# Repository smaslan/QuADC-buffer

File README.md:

# Precision Buffer with Low Input Capacitance

Following project is a precision buffer developed in scope of project EMPIR project QuADC (see documentation.pdf for details).

The main goal was flatness below 0.1 µV/V up to 10 kHz. Calibration uncertainty at 1 MHz requirement was 5 µV/V. Input capacitance as low as possible. Output impedance as low as possible. The circuit uses bootstrapping of the supply voltages which reduces errors significantly and also ensure very low apparent input shunting capacitance. Cost for the solution is limited stability. The buffer cannot be supplied from low impedance source otherwise it tends to oscillate. It designed as output bufffer for the resistive voltage dividers.

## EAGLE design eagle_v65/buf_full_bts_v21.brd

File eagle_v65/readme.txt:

Eagle files, version V6.5

Layers from top to bottom: top, route2, route15, bottom
Top silk: tPlace + tDoc + tNames
Bottom silk (not tested): bPlace + bNames

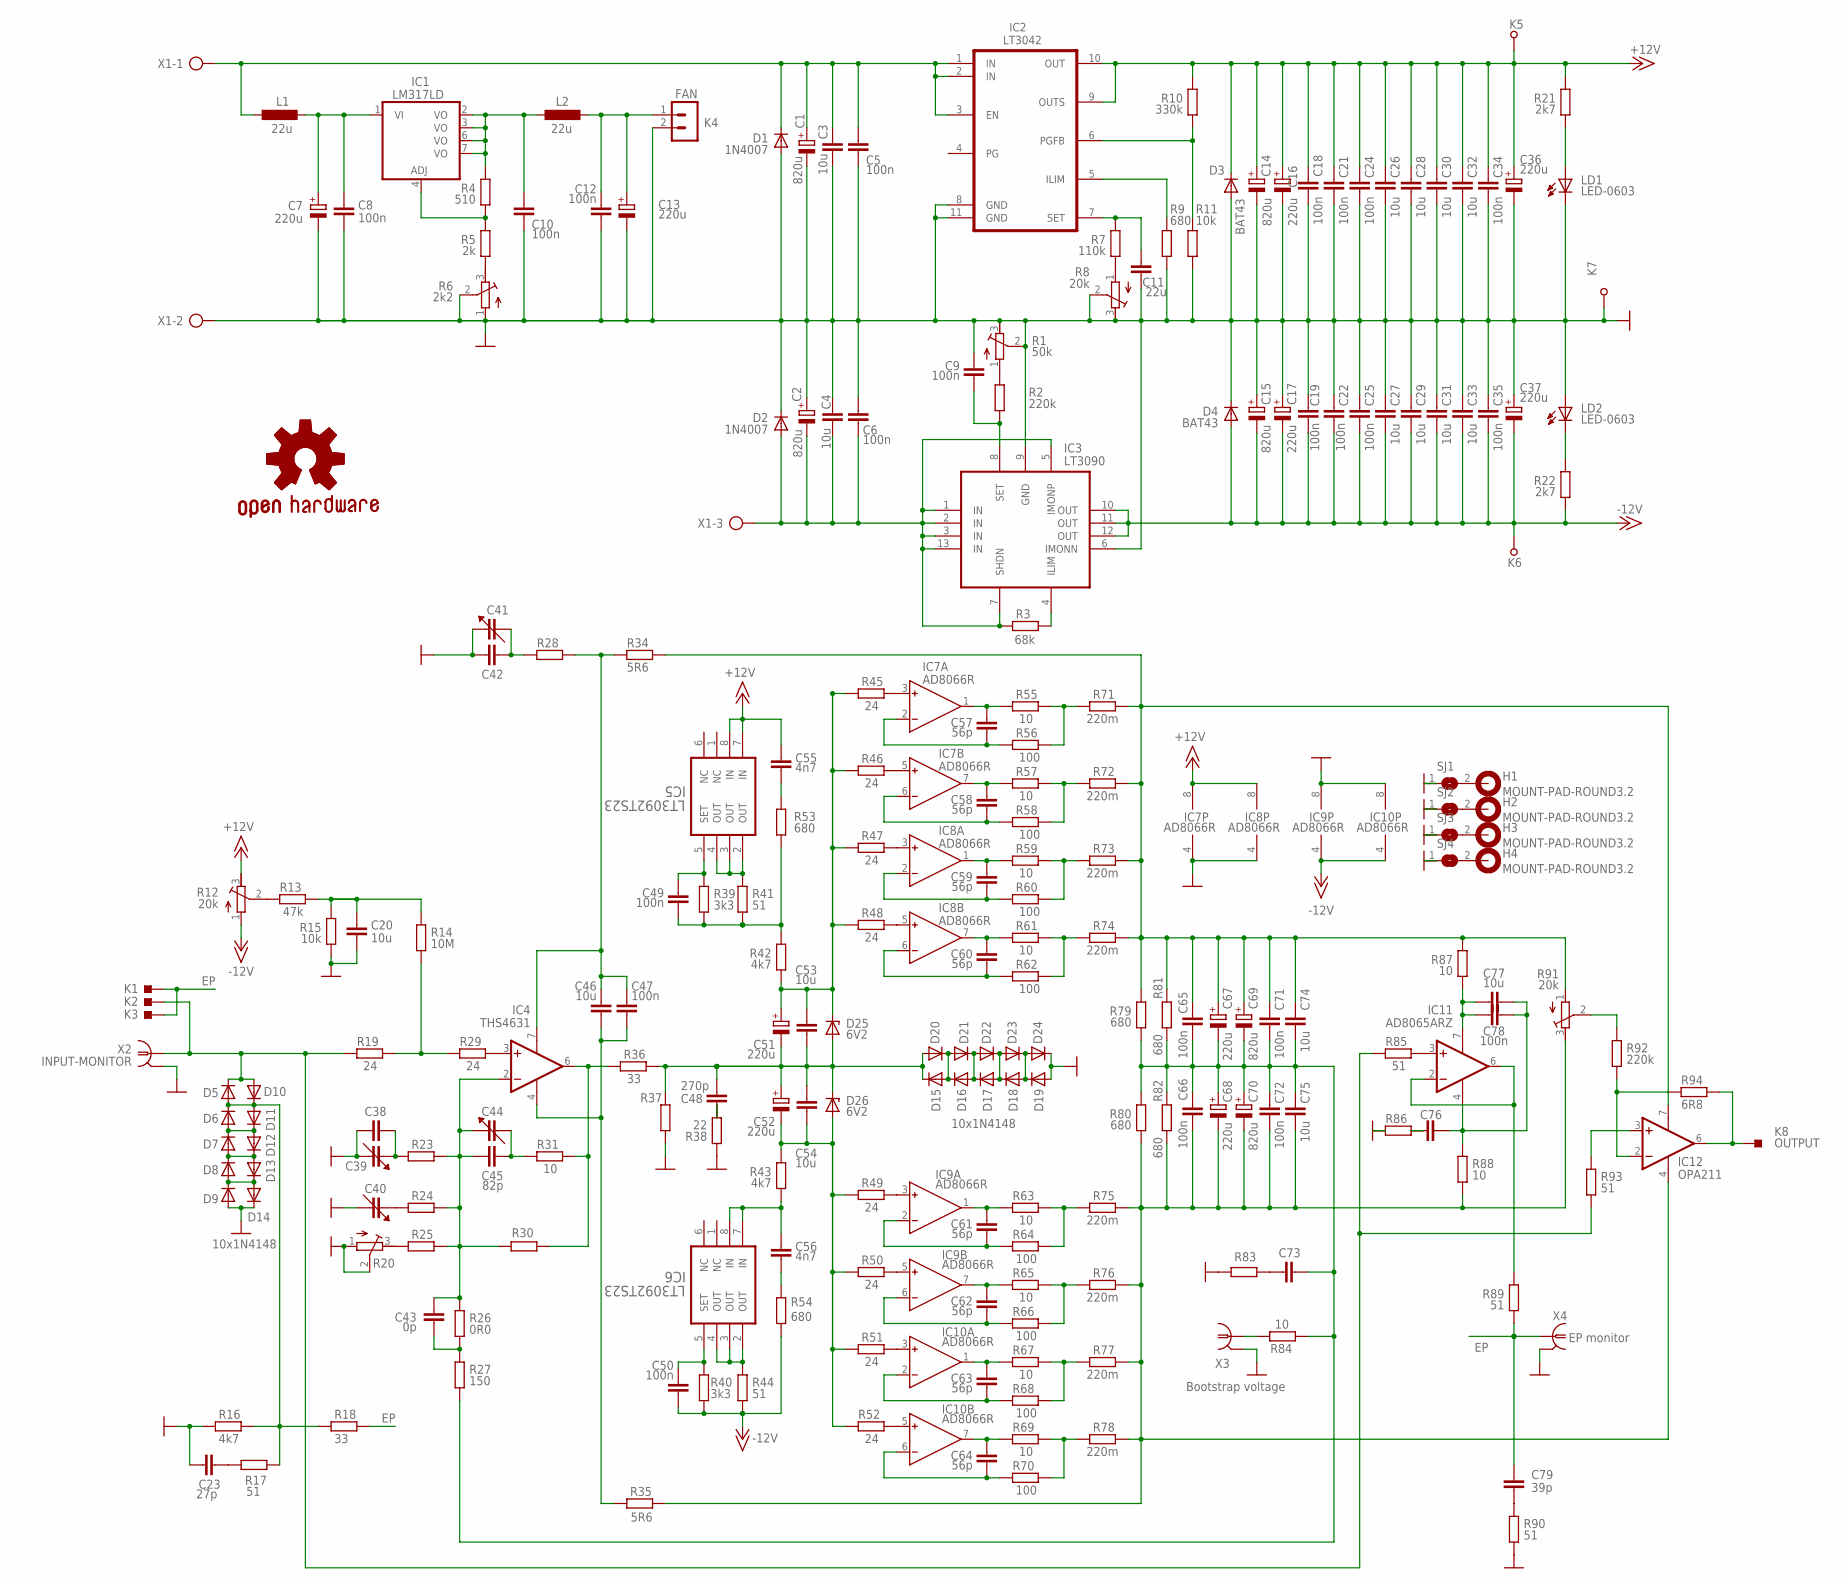
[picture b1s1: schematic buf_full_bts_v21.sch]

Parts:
C1, C2, C14, C15, C69, C70: 820u; E5-10,5
C3, C4, C20, C26, C27, C28, C29, C30, C31, C32, C33, C46, C53, C54, C74, C75, C77: 10u; C1210K
C5, C6, C8, C9, C10, C12, C18, C19, C21, C22, C24, C25, C34, C35, C47, C49, C50, C65, C66, C71, C72, C78: 100n; X0805
C7, C13, C16, C17, C36, C37, C51, C52, C67, C68: 220u; E2,5-7
C11: 22u; C1210K
C23: 27p; C025-024X044
C38, C42, C73, C76: C-EU025-024X044; C025-024X044
C39, C40, C41, C44: C_TRIMMER-9344; CTRIMMER9344
C43: 0p; C025-024X044
C45: 82p; C025-024X044
C48: 270p; X0805
C55, C56: 4n7; C025-024X044
C57, C58, C59, C60, C61, C62, C63, C64: 56p; C025-024X044
C79: 39p; C025-024X044
D1, D2: 1N4007; DO-214AC
D3, D4: BAT43; SOD80C
D5, D6, D7, D8, D9, D10, D11, D12, D13, D16, D17, D18, D19, D20, D21, D22, D23, D24: DIODE-MICROMELF-W; MICROMELF-W
D14, D15: 10x1N4148; MICROMELF-W
D25, D26: 6V2; SOD80C
GOLD_ORB_SM1: OSHWLOGO_GOLD_ORB_MED; OSHW1
H1, H2, H3, H4: MOUNT-PAD-ROUND3.2; 3,2-PAD
IC1: LM317LD; SO08
IC2: LT3042; SOP50P490X110-11N
IC3: LT3090; SOP65P490X110-13N
IC4: THS4631; SO8
IC5, IC6: LT3092TS23; SOT65P280X100-8N
IC7, IC8, IC9, IC10: AD8066R; SO8
IC11: AD8065ARZ; SO8
IC12: OPA211; SO8
K1, K3: SP_RI; SMD_1X1_S9
K2: SP_RH; SMD_1X1_S8
K4: FAN; MA02-1W
K5, K6, K7: SPP; SP_PRO
K8: OUTPUT; SMD_1X1_S8
L1, L2: 22u; L3225M
LD1, LD2: LED-0603; D0603
R1: 50k; RTRIM3214W
R2, R92: 220k; X0805
R3: 68k; X0805
R4: 510; X0805
R5: 2k; X0805
R6: 2k2; RT3364W
R7: 110k; X0805
R8, R12, R91: 20k; RTRIM3214W
R9, R79, R80, R81, R82: 680; X0805
R10: 330k; X0805
R11, R15: 10k; X0805
R13: 47k; X0805
R14: 10M; X0805
R16, R42, R43: 4k7; X0805
R17, R90: 51; 0207/2V
R18: 33; X0805
R19, R29, R45, R46, R47, R48, R49, R50, R51, R52: 24; X0805
R20: R-TRIMM3214W; RTRIM3214W
R21, R22: 2k7; X0805
R23, R24, R25, R28, R30, R37, R83, R86: R-EU_0207/2V; 0207/2V
R26: 0R0; 0207/2V
R27: 150; 0207/2V
R31, R55, R57, R59, R61, R63, R65, R67, R69, R84: 10; 0207/2V
R34, R35: 5R6; X0805
R36: 33; 0207/2V
R38: 22; X0805
R39, R40: 3k3; X0805
R41, R44, R85, R89, R93: 51; X0805
R53, R54: 680; 0207/2V
R56, R58, R60, R62, R64, R66, R68, R70: 100; 0207/2V
R71, R72, R73, R74, R75, R76, R77, R78: 220m; R1210
R87, R88: 10; X0805
R94: 6R8; X0805
SJ1, SJ2, SJ3, SJ4: SJ
X1: AK500/3
X2: INPUT-MONITOR; A1944
X3: Bootstrap voltage; A1944
X4: EP monitor; A1944

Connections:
+15V: C14.+, C16.+, C18.P$1 (1), C21.P$1 (1), C24.P$1 (1), C26.1, C28.1, C30.1, C32.1, C34.P$1 (1), C36.+, C55.1, D3.C, IC2.9 (OUTS), IC2.10 (OUT), IC5.7 (IN), IC5.8 (IN), IC7.8 (V+), IC8.8 (V+), K5.P$1, R10.P$2 (2), R12.3 (E), R21.P$2 (2)
+15V1: C56.1, IC6.7 (IN), IC6.8 (IN), R43.P$1 (1)
+15V2: C1.+, C3.1, C5.P$1 (1), D1.C, IC2.1 (IN), IC2.2 (IN), IC2.3 (EN), L1.1, X1.1
-15V: C15.-, C17.-, C19.P$2 (2), C22.P$2 (2), C25.P$2 (2), C27.2, C29.2, C31.2, C33.2, C35.P$2 (2), C37.-, C50.P$2 (2), D4.A, IC3.10 (OUT), IC3.11 (OUT), IC3.12 (OUT), IC9.4 (V-), IC10.4 (V-), K6.P$1, R12.1 (A), R22.P$1 (1), R40.P$1 (1), R44.P$1 (1), R54.1
-15V1: C2.-, C4.2, C6.P$2 (2), D2.A, IC3.1 (IN), IC3.2 (IN), IC3.3 (IN), IC3.5 (IMONP), IC3.7 (SHDN), IC3.13 (IN), R3.P$2 (2), X1.3
BTS+: C65.P$1 (1), C67.+, C69.+, C71.P$1 (1), C74.1, IC12.7 (V+), R34.P$2 (2), R71.2, R72.2, R73.2, R74.2, R79.P$2 (2), R81.P$2 (2), R87.P$2 (2), R91.1 (A)
BTS-: C66.P$2 (2), C68.-, C70.-, C72.P$2 (2), C75.2, IC12.4 (V-), R35.P$1 (1), R75.2, R76.2, R77.2, R78.2, R80.P$1 (1), R82.P$1 (1), R88.P$1 (1), R91.3 (E)
BTSG: C65.P$2 (2), C66.P$1 (1), C67.-, C68.+, C69.-, C70.+, C71.P$2 (2), C72.P$1 (1), C73.2, C74.2, C75.1, R27.2, R79.P$1 (1), R80.P$2 (2), R81.P$1 (1), R82.P$2 (2), R84.1
EP: C79.2, K1.1, K3.1, R18.P$1 (1), R89.P$1 (1), X4.1
GND: C1.-, C2.+, C3.2, C4.1, C5.P$2 (2), C6.P$1 (1), C7.-, C8.P$2 (2), C9.P$1 (1), C10.P$2 (2), C11.2, C12.P$2 (2), C13.-, C14.-, C15.+, C16.-, C17.+, C18.P$2 (2), C19.P$1 (1), C20.2, C21.P$2 (2), C22.P$1 (1), C23.1, C24.P$2 (2), C25.P$1 (1), C26.2, C27.1, C28.2, C29.1, C30.2, C31.1, C32.2, C33.1, C34.P$2 (2), C35.P$1 (1), C36.-, C37.+, C38.2, C39.2 (1), C40.2 (1), C41.1 (2), C42.1, D1.A, D2.C, D3.A, D4.C, D9.A, D14.C, D19.A, D24.C, IC2.8 (GND), IC2.11 (GND), IC3.6 (IMONN), IC3.9 (GND), IC7.4 (V-), IC8.4 (V-), IC9.8 (V+), IC10.8 (V+), K4.2, K7.P$1, LD1.K (C), LD2.A, R1.2 (S), R1.3 (E), R6.1 (A), R6.2 (S), R8.2 (S), R8.3 (E), R9.P$1 (1), R11.P$1 (1), R15.P$1 (1), R16.P$2 (2), R20.1 (A), R20.2 (S), R37.1, R38.P$1 (1), R83.1, R86.1, R90.1, SJ1.1, SJ2.1, SJ3.1, SJ4.1, X1.2, X2.2, X2.3 (2), X2.4 (2), X2.5 (2), X3.2, X3.3 (2), X3.4 (2), X3.5 (2), X4.2, X4.3 (2), X4.4 (2), X4.5 (2)
IN: D5.C, D10.A, K2.1, R19.P$1 (1), R85.P$1 (1), R93.P$1 (1), X2.1
unnamed: C59.2, IC8.2 (IN-), R60.1
unnamed: C59.1, IC8.1 (OUT), R59.1
unnamed: C60.1, IC8.7 (OUT), R61.1
unnamed: C60.2, IC8.6 (IN-), R62.1
unnamed: R61.2, R62.2, R74.1
unnamed: R59.2, R60.2, R73.1
unnamed: C57.2, IC7.2 (IN-), R56.1
unnamed: C57.1, IC7.1 (OUT), R55.1
unnamed: C58.1, IC7.7 (OUT), R57.1
unnamed: C58.2, IC7.6 (IN-), R58.1
unnamed: R57.2, R58.2, R72.1
unnamed: R55.2, R56.2, R71.1
unnamed: IC7.3 (IN+), R45.P$2 (2)
unnamed: IC7.5 (IN+), R46.P$2 (2)
unnamed: IC8.3 (IN+), R47.P$2 (2)
unnamed: IC8.5 (IN+), R48.P$2 (2)
unnamed: C63.2, IC10.2 (IN-), R68.1
unnamed: C63.1, IC10.1 (OUT), R67.1
unnamed: C64.1, IC10.7 (OUT), R69.1
unnamed: C64.2, IC10.6 (IN-), R70.1
unnamed: R69.2, R70.2, R78.1
unnamed: R67.2, R68.2, R77.1
unnamed: C61.2, IC9.2 (IN-), R64.1
unnamed: C61.1, IC9.1 (OUT), R63.1
unnamed: C62.1, IC9.7 (OUT), R65.1
unnamed: C62.2, IC9.6 (IN-), R66.1
unnamed: R65.2, R66.2, R76.1
unnamed: R63.2, R64.2, R75.1
unnamed: IC9.3 (IN+), R49.P$2 (2)
unnamed: IC9.5 (IN+), R50.P$2 (2)
unnamed: IC10.3 (IN+), R51.P$2 (2)
unnamed: IC10.5 (IN+), R52.P$2 (2)
unnamed: LD2.K (C), R22.P$2 (2)
unnamed: C51.+, C53.1, D25.C, R42.P$1 (1), R45.P$1 (1), R46.P$1 (1), R47.P$1 (1), R48.P$1 (1)
unnamed: C52.-, C54.2, D26.A, R43.P$2 (2), R49.P$1 (1), R50.P$1 (1), R51.P$1 (1), R52.P$1 (1)
unnamed: C48.P$2 (2), C51.-, C52.+, C53.2, C54.1, D15.C, D20.A, D25.A, D26.C, R36.2, R37.2
unnamed: C23.2, R17.2
unnamed: C50.P$1 (1), IC6.5 (SET), R40.P$2 (2)
unnamed: IC4.3 (+IN), R29.P$2 (2)
unnamed: IC4.6 (OUT), R30.1, R31.2, R36.1
unnamed: C46.1, C47.P$1 (1), IC4.7 (V+), R28.2, R34.P$1 (1)
unnamed: IC6.2 (OUT), IC6.3 (OUT), IC6.4 (OUT), R44.P$2 (2)
unnamed: C46.2, C47.P$2 (2), IC4.4 (V-), R35.P$2 (2)
unnamed: C49.P$1 (1), IC5.5 (SET), R39.P$2 (2)
unnamed: C41.2 (1), C42.2, R28.1
unnamed: IC5.2 (OUT), IC5.3 (OUT), IC5.4 (OUT), R41.P$2 (2)
unnamed: C43.2, R26.2, R27.1
unnamed: C49.P$2 (2), R39.P$1 (1), R41.P$1 (1), R42.P$2 (2), R53.1
unnamed: C43.1, C44.1 (2), C45.1, IC4.2 (-IN), R23.1, R24.1, R25.1, R26.1, R30.2
unnamed: IC12.3 (+IN), R93.P$2 (2)
unnamed: C56.2, R54.2
unnamed: C11.1, IC2.7 (SET), R7.P$2 (2)
unnamed: C55.2, R53.2
unnamed: R20.3 (E), R25.2
unnamed: IC12.2 (-IN), R92.P$2 (2), R94.P$1 (1)
unnamed: R91.2 (S), R92.P$1 (1)
unnamed: R7.P$1 (1), R8.1 (A)
unnamed: D7.A, D8.C, D12.C, D13.A
unnamed: D6.A, D7.C, D11.C, D12.A
unnamed: LD1.A, R21.P$1 (1)
unnamed: IC2.6 (PGFB), R10.P$1 (1), R11.P$2 (2)
unnamed: R1.1 (A), R2.P$2 (2)
unnamed: C9.P$2 (2), IC3.8 (SET), R2.P$1 (1)
unnamed: D8.A, D9.C, D13.C, D14.A
unnamed: C20.1, R13.P$2 (2), R14.P$1 (1), R15.P$2 (2)
unnamed: R12.2 (S), R13.P$1 (1)
unnamed: D5.A, D6.C, D10.C, D11.A, R16.P$1 (1), R17.1, R18.P$2 (2)
unnamed: IC3.4 (ILIM), R3.P$1 (1)
unnamed: R84.2, X3.1
unnamed: C40.1 (2), R24.2
unnamed: C38.1, C39.1 (2), R23.2
unnamed: C44.2 (1), C45.2, R31.1
unnamed: C79.1, R90.2
unnamed: C77.1, C78.P$1 (1), IC11.7 (V+), R87.P$1 (1)
unnamed: C73.1, R83.2
unnamed: IC11.3 (+IN), R85.P$2 (2)
unnamed: IC11.2 (-IN), IC11.6 (OUT), R89.P$2 (2)
unnamed: C76.2, C77.2, C78.P$2 (2), IC11.4 (V-), R88.P$2 (2)
unnamed: C76.1, R86.2
unnamed: H1.B3,2, SJ1.2
unnamed: H2.B3,2, SJ2.2
unnamed: H3.B3,2, SJ3.2
unnamed: H4.B3,2, SJ4.2
unnamed: R14.P$2 (2), R19.P$2 (2), R29.P$1 (1)
unnamed: C10.P$1 (1), IC1.2 (VO), IC1.3 (VO), IC1.6 (VO), IC1.7 (VO), L2.1, R4.P$2 (2)
unnamed: IC1.4 (ADJ), R4.P$1 (1), R5.P$2 (2)
unnamed: C48.P$1 (1), R38.P$2 (2)
unnamed: C12.P$1 (1), C13.+, K4.1, L2.2
unnamed: R5.P$1 (1), R6.3 (E)
unnamed: C7.+, C8.P$1 (1), IC1.1 (VI), L1.2
unnamed: D18.A, D19.C, D23.C, D24.A
unnamed: D17.A, D18.C, D22.C, D23.A
unnamed: D16.A, D17.C, D21.C, D22.A
unnamed: D15.A, D16.C, D20.C, D21.A
unnamed: IC2.5 (ILIM), R9.P$2 (2)
OUT: IC12.6 (OUT), K8.1, R94.P$2 (2)

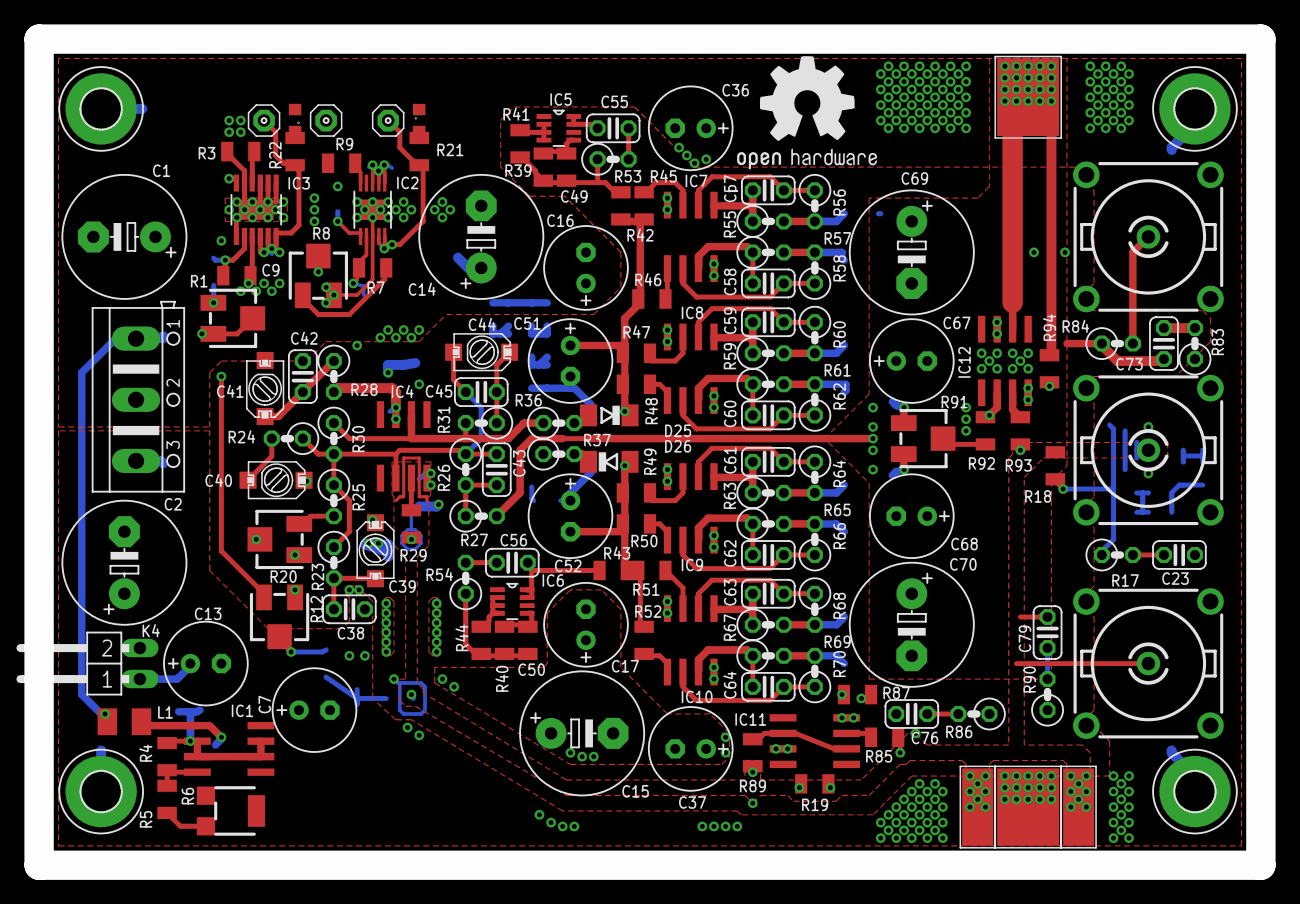
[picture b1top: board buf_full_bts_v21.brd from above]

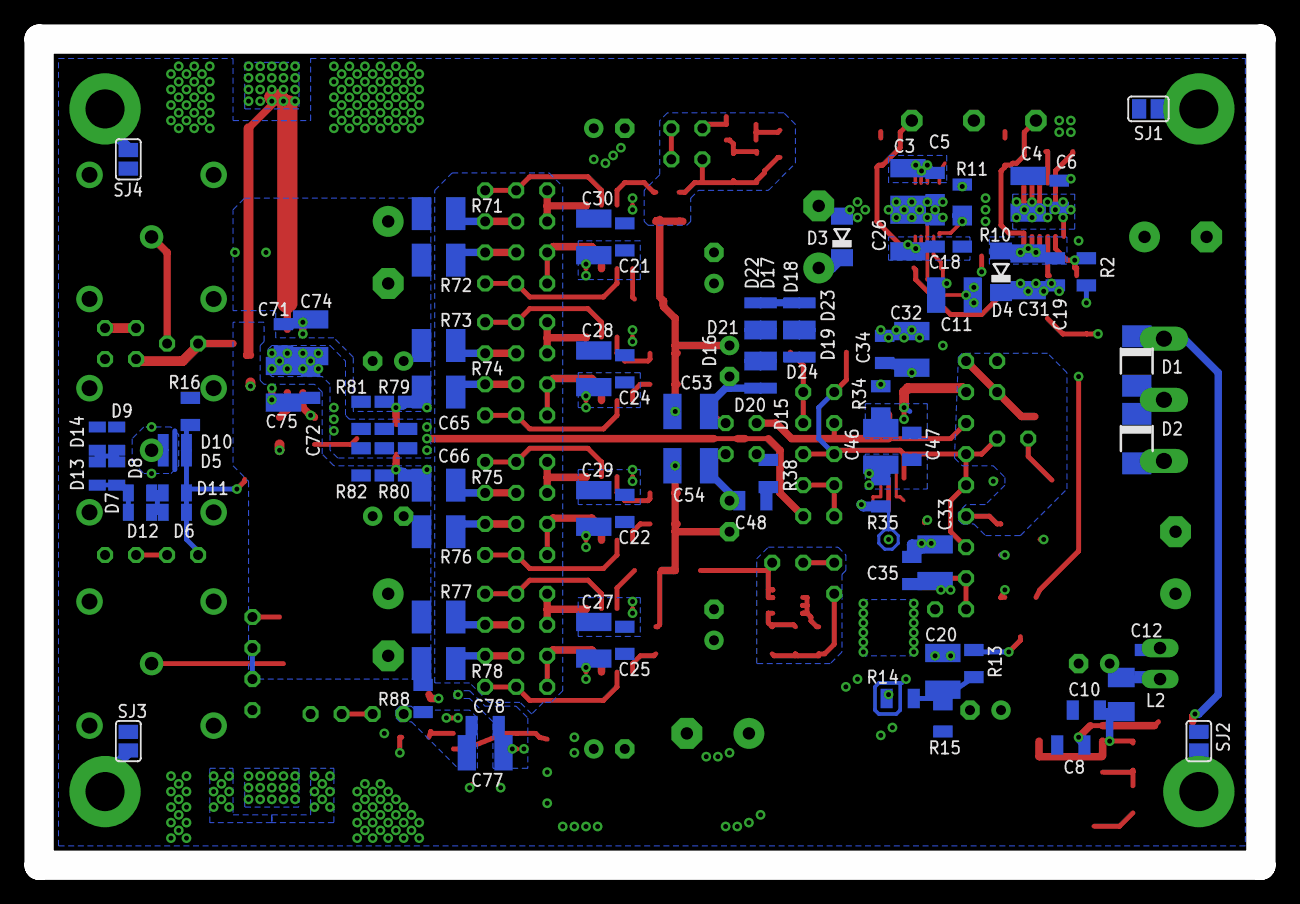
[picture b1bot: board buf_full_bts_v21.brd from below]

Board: 4 copper layers, 100.0 x 67.6 mm, 234 parts (90 on the bottom side), 107 nets.

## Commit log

2018-06-06 add: initial commit

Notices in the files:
eagle_v65/buf_full_bts_v21.brd:
CERN OHL license V1.2
